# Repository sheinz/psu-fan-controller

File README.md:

Power supply fan controller
===========================

Many lab power supplies have annoying fans that spins all the time.
The fan produces noise even though the power supply usually works with small
currents and do not heat up at all. This mod turns on the fan only when
it is needed, when temperature of the heatsink is rising.

## Features

 * Use temperature sensor to gradually increase fan speed
 * Easy configurable temperature and fan speed table
 * Test fan on start-up
 * Uses LM35 temperature sensor

## Schematic

## Licence

MIT

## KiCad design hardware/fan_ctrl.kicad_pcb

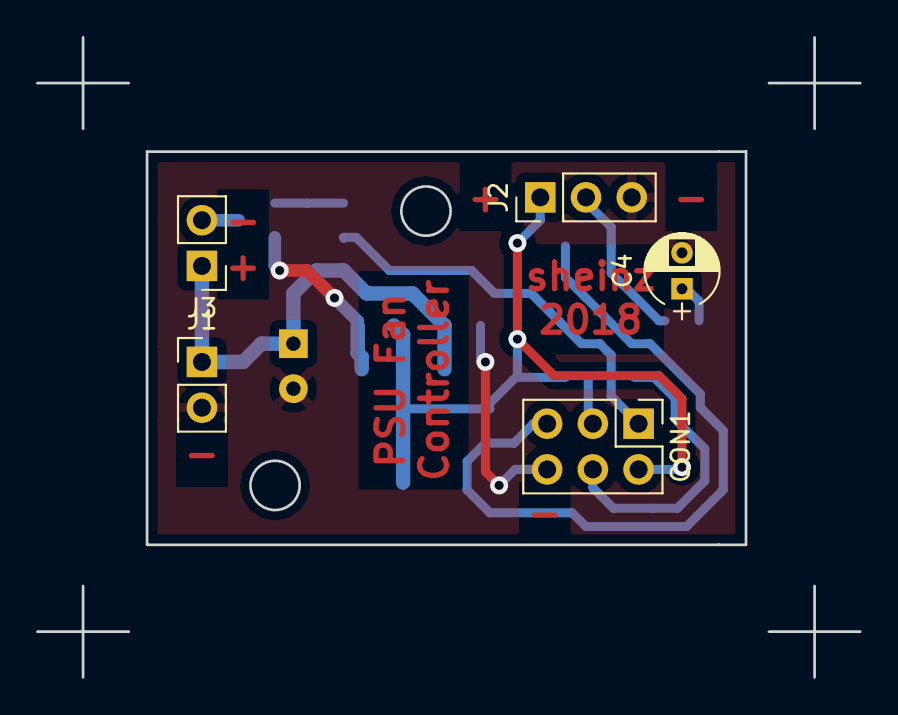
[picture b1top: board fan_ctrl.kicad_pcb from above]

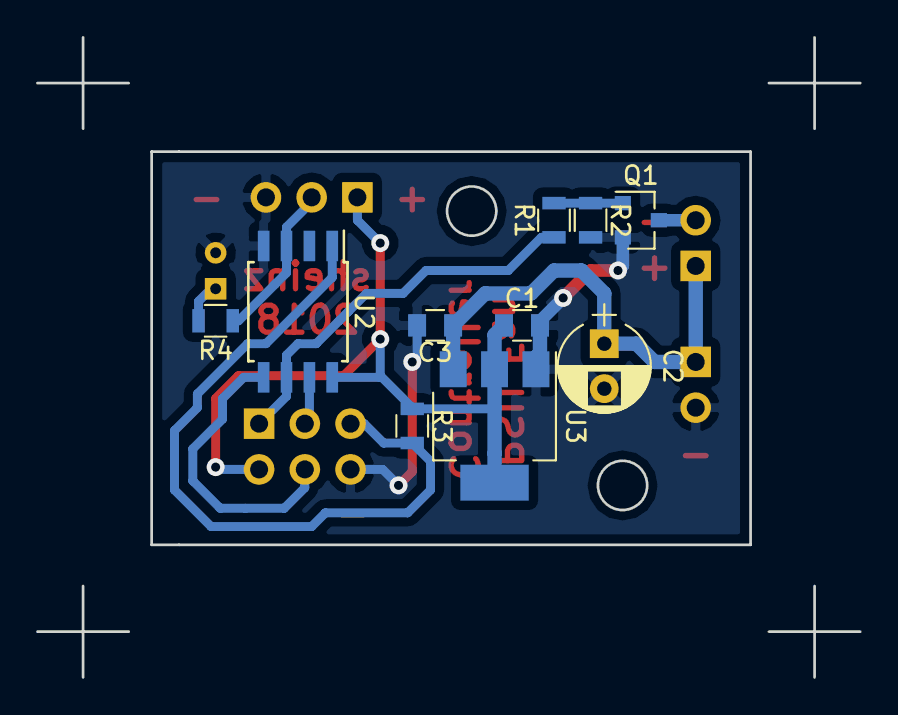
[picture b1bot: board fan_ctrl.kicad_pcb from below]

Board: 2 copper layers, 33.3 x 21.8 mm, 15 parts (10 on the bottom side), 11 nets.

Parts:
C1, C3: 0.1u; C_0805
C2: 47u 25v; CP_Radial_D5.0mm_P2.50mm
C4: 1u; CP_Radial_D4.0mm_P2.00mm
CON1: AVR-ISP-6; Pin_Header_Straight_2x03_Pitch2.54mm
J1: Power; Pin_Header_Straight_1x02_Pitch2.54mm
J2: LM35; Pin_Header_Straight_1x03_Pitch2.54mm
J3: Fan; Pin_Header_Straight_1x02_Pitch2.54mm
Q1: IRLML0030; SOT-23
R1: 470; R_0805
R2, R3: 10k; R_0805
R4: 75; R_0805
U2: ATTINY13A-SU; SOIJ-8_5.3x5.3mm_Pitch1.27mm
U3: AP1117-50; SOT-223-3_TabPin2

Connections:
/12V: C2.1, C3.1, J1.1, J3.1, U3.3
GND: C1.2, C2.2, C3.2, C4.2, CON1.6, J1.2, J2.3, Q1.2, R2.2, U2.4, U3.1
unnamed: C4.1, R4.2
unnamed: CON1.1, R1.1, U2.6
unnamed: CON1.3, U2.7
unnamed: CON1.4, U2.5
unnamed: CON1.5, R3.2, U2.1
unnamed: J2.2, R4.1, U2.3
unnamed: J3.2, Q1.3
unnamed: Q1.1, R1.2, R2.1
VCC: C1.1, CON1.2, J2.1, R3.1, U2.8, U3.2

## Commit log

2018-02-07 Initial implementation
2018-02-07 Added README.md
2018-02-07 Spell errors correction in README.md
